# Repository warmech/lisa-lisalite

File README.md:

# Lisa Lite

The Lisa Lite is an adapter card for the Lisa 2 and 2/5 that allows a Twiggy drive to be replaced by a 400K Sony 3.5" floppy drive. Most of the signals are passed directly from the Twiggy interface to the Sony interface, though the motor clock signal on the Twiggy side is used as the basis (along with a 5MHz oscillator) for generating the PWM signal used to drive the Sony drive.

## Assembly

There is little to explain in terms of assembly, as the card uses relative few components. It should be noted that it is recommended to use keyed connectors for the Twiggy and Sony ribbon cable connectors. Inserting the cables backwards will result in the +12V power rail being piped into the CA0, CA1, CA2, and LSTRB lines on the Sony drive and the READ and MTRCLK lines on the Twiggy interface; this will likely destroy any ICs on these lines and possibly other passive and/or electromechanical components.

## Use

There is also little to explain in terms of installation and use. The Lisa Lite fastens into two standoffs on the side of the internal drive cage closest to the monitor. The wide Twiggy ribbon cable connects to the interface at the rear of the card and the narrow ribbon cable to the interface in the card's middle. A socket may be used for the oscillator if desired, though it's not necessary by any means.

Once the card is installed and connected, no further action is required for use; the card is effectively a passive component itself and the Lisa ROM/IWM manages interfacing with the Sony drive.

## Miscellany

This card is unnecessary on a 2/10, which uses an IC on the I/O card to handle communications with a Sony drive. Additionally, an 800K drive may be used in conjunction with a Sun Remarketing ROM intended for use with the Macintosh XL.

This is a very simple design that I would like to eventually replace with a small CPLD for use in an ATX form-factor Lisa. As it's so tiny a circuit, the Verilog required for this practically writes itself.

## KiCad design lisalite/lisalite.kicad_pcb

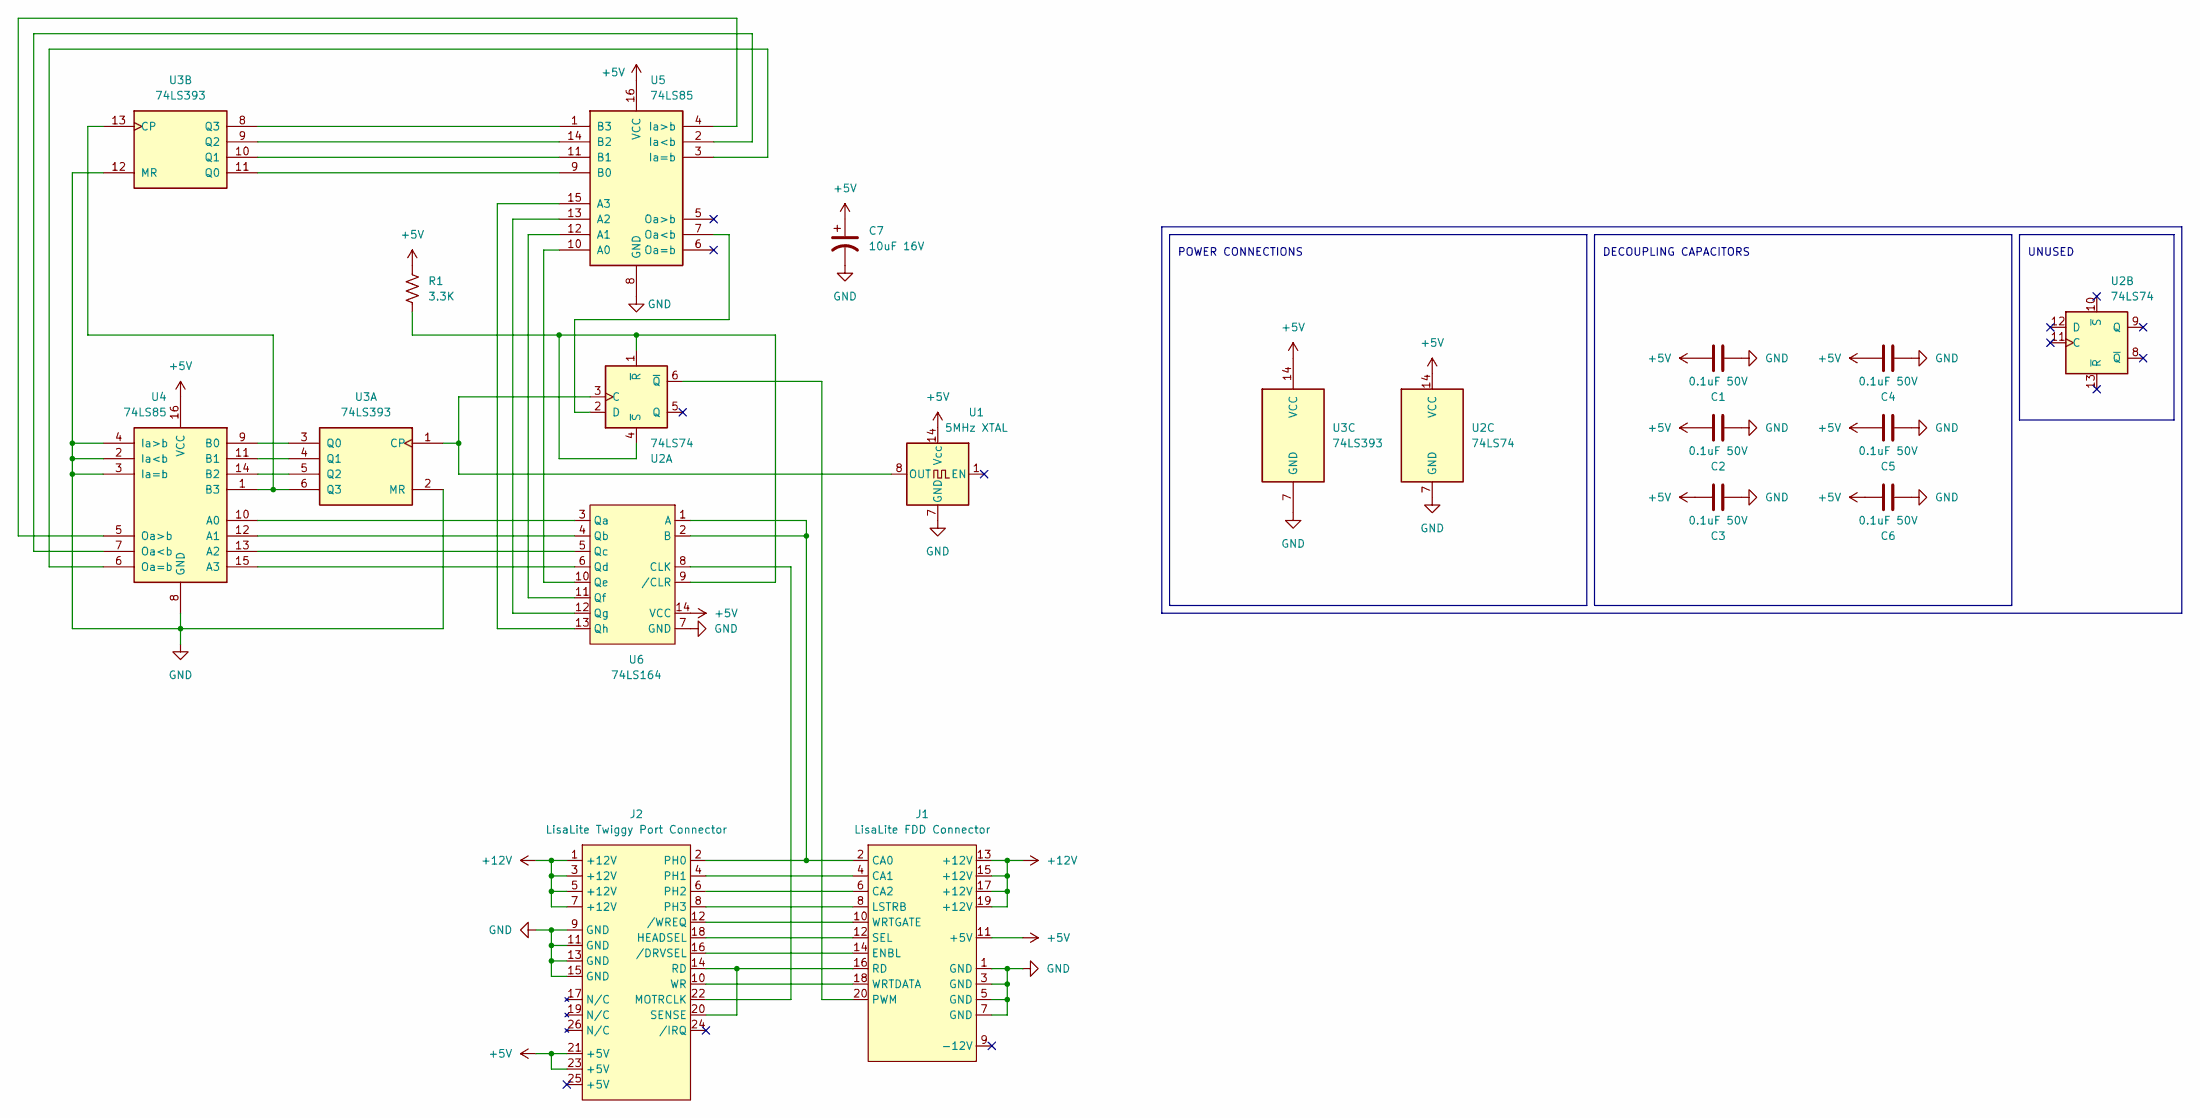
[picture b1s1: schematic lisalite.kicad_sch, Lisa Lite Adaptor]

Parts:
C1, C2, C3, C4, C5, C6: 0.1uF 50V; C_Axial_L3.8mm_D2.6mm_P10.00mm_Horizontal
C7: 10uF 16V; CP_Axial_L10.0mm_D6.0mm_P15.00mm_Horizontal
J1: LisaLite FDD Connector; PinHeader_2x10_P2.54mm_Vertical
J2: LisaLite Twiggy Port Connector; PinHeader_2x13_P2.54mm_Vertical
R1: 3.3K; R_Axial_DIN0309_L9.0mm_D3.2mm_P12.70mm_Horizontal
U1: 5MHz XTAL; DIP-14_W7.62mm
U2: 74LS74
U3: 74LS393; DIP-14_W7.62mm
U4, U5: 74LS85; DIP-16_W7.62mm
U6: 74LS164; DIP-14_W7.62mm

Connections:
+5V: C1.2, C2.2, C3.2, C4.2, C5.2, C6.2, C7.1, J1.11 (+5V), J2.21 (+5V), J2.23 (+5V), R1.1, U1.14 (Vcc), U2.14 (VCC), U3.14 (VCC), U4.16 (VCC), U5.16 (VCC), U6.14 (VCC)
+12V: J1.13 (+12V), J1.15 (+12V), J1.17 (+12V), J1.19 (+12V), J2.1 (+12V), J2.3 (+12V), J2.5 (+12V), J2.7 (+12V)
GND: C1.1, C2.1, C3.1, C4.1, C5.1, C6.1, C7.2, J1.1 (GND), J1.3 (GND), J1.5 (GND), J1.7 (GND), J2.9 (GND), J2.11 (GND), J2.13 (GND), J2.15 (GND), U1.7 (GND), U2.7 (GND), U3.2 (MR), U3.7 (GND), U3.12 (MR), U4.2 (Ia<b), U4.3 (Ia=b), U4.4 (Ia>b), U4.8 (GND), U5.8 (GND), U6.7 (GND)
unnamed: J1.2 (CA0), J2.2 (PH0), U6.1 (A), U6.2 (B)
unnamed: J1.4 (CA1), J2.4 (PH1)
unnamed: J1.6 (CA2), J2.6 (PH2)
unnamed: J1.14 (ENBL), J2.16 (/DRVSEL)
unnamed: J1.8 (LSTRB), J2.8 (PH3)
unnamed: J1.20 (PWM), U2.6 (~Q)
unnamed: J1.16 (RD), J2.14 (RD), J2.20 (SENSE)
unnamed: J1.12 (SEL), J2.18 (HEADSEL)
unnamed: J1.18 (WRTDATA), J2.10 (WR)
unnamed: J1.10 (WRTGATE), J2.12 (/WREQ)
unnamed: J2.22 (MOTRCLK), U6.8 (CLK)
unnamed: U1.8 (OUT), U2.3 (C), U3.1 (CP)
unnamed: U2.2 (D), U5.7 (Oa<b)
unnamed: R1.2, U2.1 (~R), U2.4 (~S), U6.9 (/CLR)
unnamed: U3.3 (Q0), U4.9 (B0)
unnamed: U3.4 (Q1), U4.11 (B1)
unnamed: U3.5 (Q2), U4.14 (B2)
unnamed: U3.6 (Q3), U3.13 (CP), U4.1 (B3)
unnamed: U3.11 (Q0), U5.9 (B0)
unnamed: U3.10 (Q1), U5.11 (B1)
unnamed: U3.9 (Q2), U5.14 (B2)
unnamed: U3.8 (Q3), U5.1 (B3)
unnamed: U4.10 (A0), U6.3 (Qa)
unnamed: U4.12 (A1), U6.4 (Qb)
unnamed: U4.13 (A2), U6.5 (Qc)
unnamed: U4.15 (A3), U6.6 (Qd)
unnamed: U4.7 (Oa<b), U5.2 (Ia<b)
unnamed: U4.6 (Oa=b), U5.3 (Ia=b)
unnamed: U4.5 (Oa>b), U5.4 (Ia>b)
unnamed: U5.10 (A0), U6.10 (Qe)
unnamed: U5.12 (A1), U6.11 (Qf)
unnamed: U5.13 (A2), U6.12 (Qg)
unnamed: U5.15 (A3), U6.13 (Qh)

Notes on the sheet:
UNUSED
DECOUPLING CAPACITORS
POWER CONNECTIONS

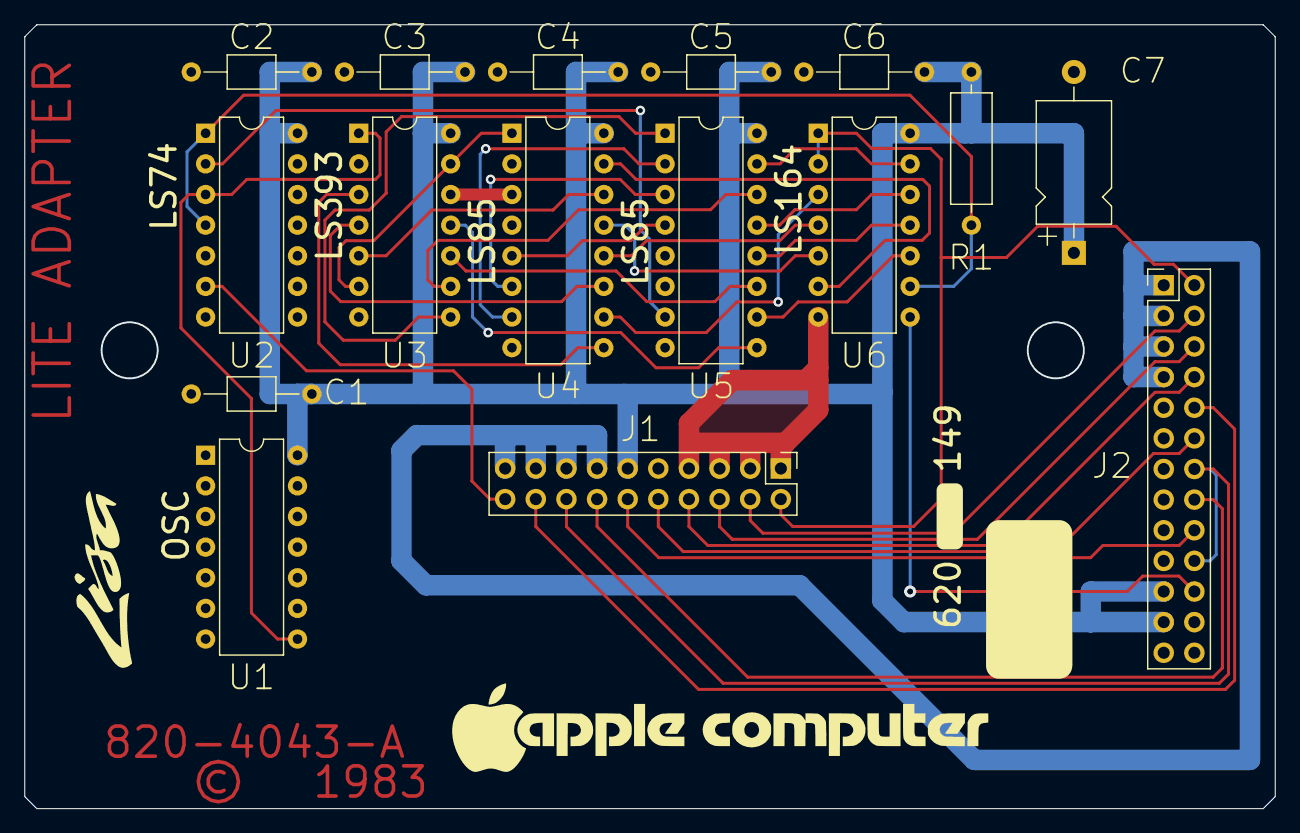
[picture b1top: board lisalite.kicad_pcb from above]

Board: 2 copper layers, 103.7 x 65.0 mm, 16 parts (0 on the bottom side), 36 nets.

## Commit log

2023-12-12 init schematic
2023-12-13 schematic updates
2024-01-08 generated pcb
2024-01-10 final commit for rev 1.0
2024-01-10 readme and cad dir rename
2024-01-10 final silkscreen adds; re-rendered images
2024-01-10 prune backups
2025-10-20 Removed junk metadata files from project

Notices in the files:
lisalite/lisalite.kicad_pcb:
© 1983
